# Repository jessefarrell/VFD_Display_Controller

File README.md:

<!-- PROJECT LOGO -->
<br />
<div align="center">

  <h1 align="center">VFD Module Controller - REV00</h1>

  <p align="center">
    The <a href="https://ckm-content.se.com/ckmContent/sfc/servlet.shepherd/document/download/0691H00000GYmavQAD">Power Measurement, ACM 3710</a> was a power meter released in 1989 which was discontinued in the "early 2000s".<br />
    These meters used an interesting, semi-custom, 20 character, 14 segment, Vacuum Fluorescent Display.
    <br />
    I have five of these VFD modules floating around my parts bin... so I made this controller board to interfce with them.
    <br />
    <br />
    <strong>STATUS - IN PROGRESS</strong>
    <br />
    <a href="https://youtube.com">View Demo</a> [PENDING]

  </p>
</div>

## Introduction
<!-- High level overview of what the project is and does -->
This VFD module controller was designed around a VFD module that was originally integrated into the <a href="https://ckm-content.se.com/ckmContent/sfc/servlet.shepherd/document/download/0691H00000GYmavQAD">ACM 3710</a>. Exact model numbers of the module seem to vary, but as far as I can tell they are all interchangeable. This module is the **ISE Electronics Corp, FU209SCPB-S4A** or **FU209SCPB-T60A**, and they seem to be a custom (undocumented) model that is similar to  **CU209SCPB-T20A**. The purpose of this project is to convert the VFD modules parallel bus interface into something configurable over USB, and to possible develop a few applications for the display.

## Motivation
<!-- Why I bothered making this -->
I'm a sucker for 7-segment displays and other interesting displays in general. So 14 segments on a VFD easily got my attention from the bin. A short dumpster dive later I found myself the proud owner of 5 VFD modules. All of the hard work of interfacing with the display is managed by the module, but I still need a way of controlling the 8bit data bus from the comfort of my desk. The fact that so much of the work has been offloaded onto the VFD module itself, makes this whole thing a good candidate for a "quick weekend project"...

## Features
- USB Serial Control
- Command Line Interface
- Write Character or String
- Shift Displayed String
- Delete Character
- Clear Screen

## How it Works
<!-- IMAGE: Block diagram -->
This project could, in theory, be as simple as a microcontroller driving the various I/O pins of the VFD module. The module itself consumes about 430-460mA during normal operation, from a single 5V power input (the module then converts that to a higher voltage for the VFD), leaving just enough headroom in the 500mA (5 unit load) USB spec to power the controller board I'm designing. Some flavour of AVR microcontroller would have been a good fit here, but my bin full of Pi Pico's is looking for a project, meaning I'll need some logic level translators. I also decided to include an optional barrel jack power input incase I want to stack multiple VFD modules together, or if the USB port isn't able to provide the 500mA.
<br />
<br />
Instead of providing a block diagram, this project is small enough to just review the schematic (shown below).

## Gallery

<!-- IMAGE: 2-3 supporting shots — schematic snippet, PCB layout, alternate angle render -->

## Status
I received PCBs 8/16/2026, and I recently ordered the connectors. This project will probably be closed later this month.

## License

---

Designed by Jesse Farrell — [info@shamrockcircuits.com](mailto:info@shamrockcircuits.com)

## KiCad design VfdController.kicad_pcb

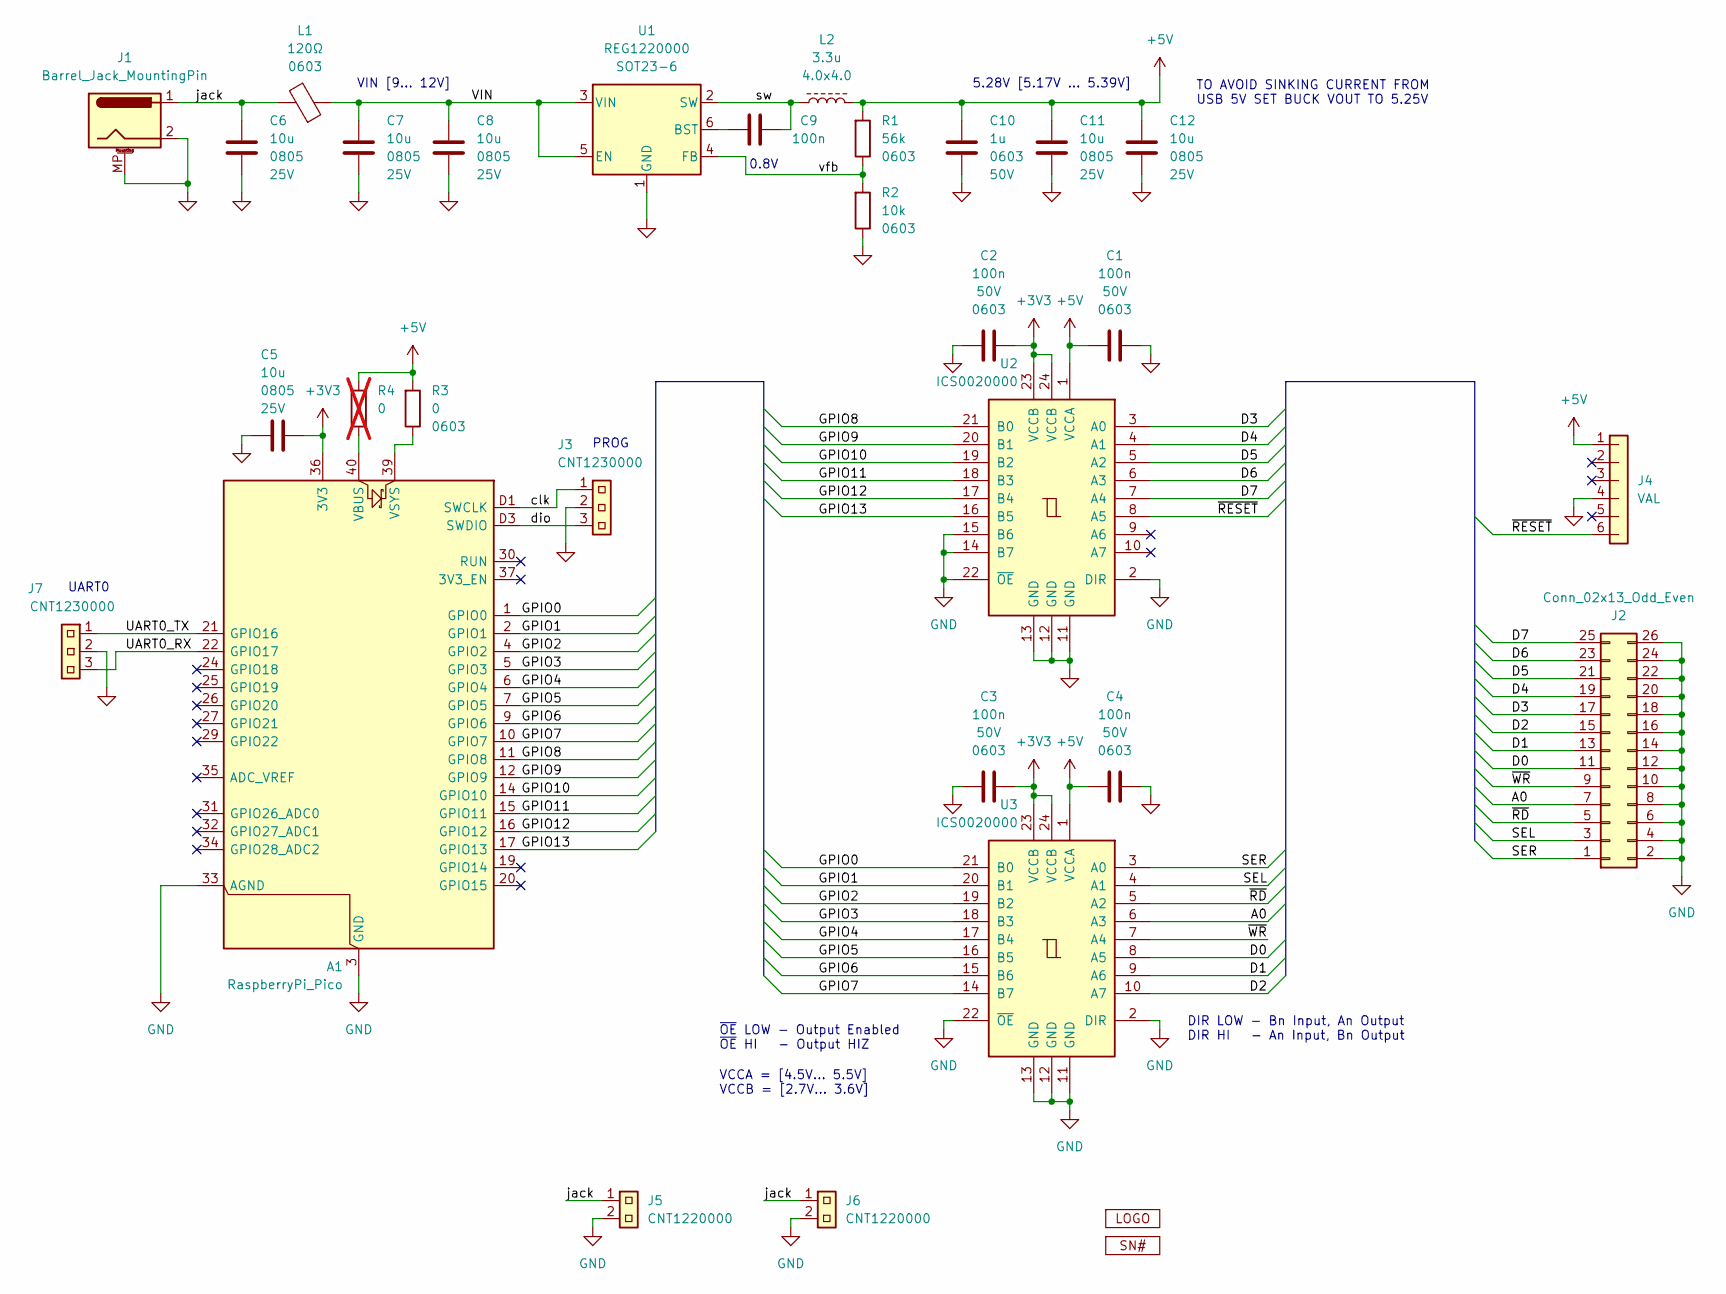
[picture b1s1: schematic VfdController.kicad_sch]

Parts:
A1: RaspberryPi_Pico; RaspberryPi_Pico_SMD_HandSolder
C1, C2, C3, C4: 100n; FTP-CAP-0001; Voltage Rating 50V; MPN_1 CC0603KRX7R9BB104; LCSC_1 C14663, BASIC
C5, C6, C7, C8, C11, C12: 10u; FTP-CAP-0002; Voltage Rating 25V; MPN_1 CL21A106KAYNNNE; LCSC_1 C15850
C9: 100n; FTP-CAP-0000; Voltage Rating 50V; MPN_1 CL05B104KB54PNC; LCSC_1 C307331
C10: 1u; FTP-CAP-0001; Voltage Rating 50V; MPN_1 CL10A105KB8NNNC; LCSC_1 C15849
G1: FTP-MRK-0002b
G2: FTP-MRK-0000
J1: Barrel_Jack_MountingPin; BarrelJack_GCT_DCJ200-10-A_Horizontal
J2: Conn_02x13_Odd_Even; IDC-Header_2x13_P2.54mm_Vertical
J3, J7: CNT1230000; FTP-CNT-0008; MPN_1 22284030; LCSC_1 C587036, EXT
J4: VAL; Molex_KK-396_A-41792-0006_1x06_P3.96mm_Horizontal
J5, J6: CNT1220000; FTP-CNT-0007; MPN_1 22284020; LCSC_1 C234182, EXT
L1: 120Ω; FTP-IND-0002; MPN_2 742792625; LCSC_1 C14709
L2: 3.3u; FTP-IND-0000; MPN_3 AWVF004040183R3M00; LCSC_3 C17220294
R1: 56k; FTP-RES-0001; MPN_1 RNCF0603BTE56K0; LCSC_1 C3958730
R2: 10k; FTP-RES-0001; MPN_1 RNCF0603BTE10K0; LCSC_1 C346560
R3: 0; FTP-RES-0001; MPN_1 0603WAF0000T5E; LCSC_1 C21189, BASIC
R4: 0; FTP-RES-0001; MPN_1 0603WAF0000T5E; LCSC_1 C21189, BASIC; not fitted
U1: REG1220000; Generic-SOT23-6; MPN_1 AP62150WU*; LCSC_1 C3194237
U2, U3: ICS0020000; Generic-TSSOP-24_4.4x7.8mm_P0.65mm; MPN_1 74LVC4245APW,118; LCSC_1 C6091, EXT

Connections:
+3V3: A1.36 (3V3), C2.2, C3.2, C5.1, U2.23 (VCCB), U2.24 (VCCB), U3.23 (VCCB), U3.24 (VCCB)
+5V: C1.1, C4.1, C10.1, C11.1, C12.1, J4.1, L2.2, R1.1, R3.1, R4.1, U2.1 (VCCA), U3.1 (VCCA)
/A0: J2.7, U3.6 (A3)
/D0: J2.11, U3.8 (A5)
/D1: J2.13, U3.9 (A6)
/D2: J2.15, U3.10 (A7)
/D3: J2.17, U2.3 (A0)
/D4: J2.19, U2.4 (A1)
/D5: J2.21, U2.5 (A2)
/D6: J2.23, U2.6 (A3)
/D7: J2.25, U2.7 (A4)
/GPIO0: A1.1 (GPIO0), U3.21 (B0)
/GPIO1: A1.2 (GPIO1), U3.20 (B1)
/GPIO2: A1.4 (GPIO2), U3.19 (B2)
/GPIO3: A1.5 (GPIO3), U3.18 (B3)
/GPIO4: A1.6 (GPIO4), U3.17 (B4)
/GPIO5: A1.7 (GPIO5), U3.16 (B5)
/GPIO6: A1.9 (GPIO6), U3.15 (B6)
/GPIO7: A1.10 (GPIO7), U3.14 (B7)
/GPIO8: A1.11 (GPIO8), U2.21 (B0)
/GPIO9: A1.12 (GPIO9), U2.20 (B1)
/GPIO10: A1.14 (GPIO10), U2.19 (B2)
/GPIO11: A1.15 (GPIO11), U2.18 (B3)
/GPIO12: A1.16 (GPIO12), U2.17 (B4)
/GPIO13: A1.17 (GPIO13), U2.16 (B5)
/SEL: J2.3, U3.4 (A1)
/SER: J2.1, U3.3 (A0)
/UART0_RX: A1.22 (GPIO17), J7.3
/UART0_TX: A1.21 (GPIO16), J7.1
/VIN: C7.1, C8.1, L1.1, U1.3 (VIN), U1.5 (EN)
/clk: A1.D1 (SWCLK), J3.1
/dio: A1.D3 (SWDIO), J3.3
/jack: C6.1, J1.1, J5.1, J6.1, L1.2
/sw: C9.1, L2.1, U1.2 (SW)
/vfb: R1.2, R2.1, U1.4 (FB)
/~RD: J2.5, U3.5 (A2)
/~RESET: J4.6, U2.8 (A5)
/~WR: J2.9, U3.7 (A4)
GND: A1.3 (GND), A1.8 (GND), A1.13 (GND), A1.18 (GND), A1.23 (GND), A1.28 (GND), A1.33 (AGND), A1.38 (GND), A1.D2 (GND), C1.2, C2.1, C3.1, C4.2, C5.2, C6.2, C7.2, C8.2, C10.2, C11.2, C12.2, J1.2, J1.MP (MountPin_MP), J2.2, J2.4, J2.6, J2.8, J2.10, J2.12, J2.14, J2.16, J2.18, J2.20, J2.22, J2.24, J2.26, J3.2, J4.4, J5.2, J6.2, J7.2, R2.2, U1.1 (GND), U2.2 (DIR), U2.11 (GND), U2.12 (GND), U2.13 (GND), U2.14 (B7), U2.15 (B6), U2.22 (~OE), U3.2 (DIR), U3.11 (GND), U3.12 (GND), U3.13 (GND), U3.22 (~OE)
unnamed: A1.40 (VBUS), R4.2
unnamed: A1.39 (VSYS), R3.2
unnamed: C9.2, U1.6 (BST)

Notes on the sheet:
DIR LOW - Bn Input, An Output DIR HI - An Input, Bn Output
VCCA = [4.5V... 5.5V] VCCB = [2.7V... 3.6V]
5.28V [5.17V ... 5.39V]
PROG
0.8V
~{OE} LOW - Output Enabled ~{OE} HI - Output HIZ
UART0
TO AVOID SINKING CURRENT FROM USB 5V SET BUCK VOUT TO 5.25V
VIN [9... 12V]

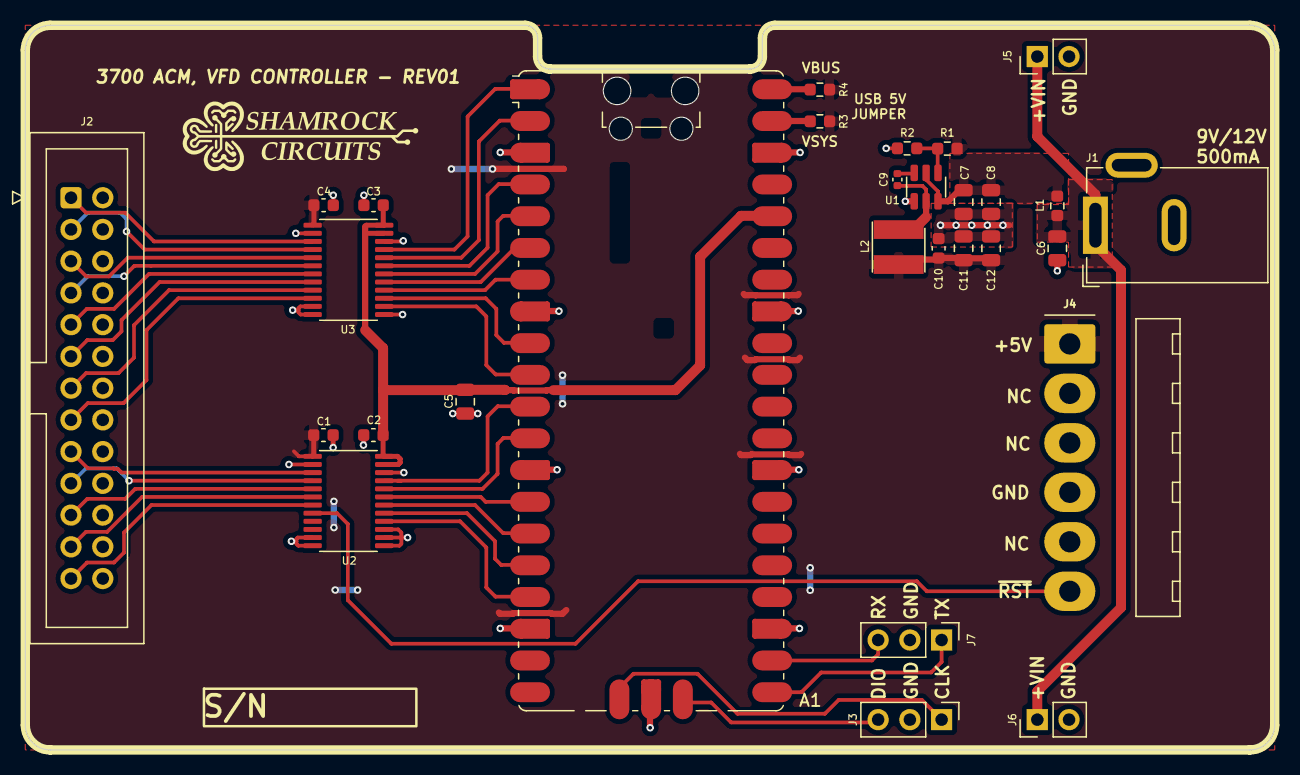
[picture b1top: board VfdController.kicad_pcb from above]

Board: 2 copper layers, 100.0 x 58.0 mm, 31 parts (0 on the bottom side), 42 nets.

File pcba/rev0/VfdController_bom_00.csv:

IPN,Reference,Qty,Value,Exclude from BOM,Footprint,Package,MFN_1,MPN_1,LCSC_1
N/A,A1,1,RaspberryPi_Pico,,Module:RaspberryPi_Pico_SMD_HandSolder,,,,
CAP-000-1042,"C1,C2,C3,C4",4,100n,,0-CAP:FTP-CAP-0001,603,Samsung,CC0603KRX7R9BB104,"C14663, BASIC"
CAP-007-1061,"C5,C6,C7,C8,C11,C12",6,10u,,0-CAP:FTP-CAP-0002,805,Samsung,CL21A106KAYNNNE,C15850
CAP-001-1042,C9,1,100n,,0-CAP:FTP-CAP-0000,402,Samsung,CL05B104KB54PNC,C307331
CAP-003-1051,C10,1,1u,,0-CAP:FTP-CAP-0001,603,Samsung,CL10A105KB8NNNC,C15849
N/A,J1,1,Barrel_Jack_MountingPin,,Connector_BarrelJack:BarrelJack_GCT_DCJ200-10-A_Horizontal,,,,
N/A,J2,1,Conn_02x13_Odd_Even,,Connector_IDC:IDC-Header_2x13_P2.54mm_Vertical,,,,
CNT-123-0000,J3,1,CNT1230000,,0-CNT:FTP-CNT-0008,,Molex,22284030,"C587036, EXT"
N/A,J4,1,VAL,,Connector_Molex:Molex_KK-396_A-41792-0006_1x06_P3.96mm_Horizontal,,,,
CNT-122-0000,"J5,J6",2,CNT1220000,,0-CNT:FTP-CNT-0007,,Molex,22284020,"C234182, EXT"
IND-203-1202,L1,1,120Ω,,0-IND:FTP-IND-0002,603,Murata,BLM18PG121SN1D,C14709
IND-002-3304,L2,1,3.3u,,0-IND:FTP-IND-0000,4.0x4.0,Vishay,VLS4020CX-3R3M-H,C6745793
RES-006-5604,R1,1,56k,,0-RES:FTP-RES-0001,603,Stackpole Electronics,RNCF0603BTE56K0,C3958730
RES-006-1004,R2,1,10k,,0-RES:FTP-RES-0001,603,Stackpole Electronics,RNCF0603BTE10K0,C346560
RES-000-0000,R3,1,0,,0-RES:FTP-RES-0001,603,UNI-ROYAL,0603WAF0000T5E,"C21189, BASIC"
REG-122-0000,U1,1,REG1220000,,1-PACKAGES:Generic-SOT23-6,SOT23-6,Diodes Inc.,AP62150WU*,C3194237
ICS-002-0000,"U2,U3",2,ICS0020000,,1-PACKAGES:Generic-TSSOP-24_4.4x7.8mm_P0.65mm,TSSOP-24 (4.40mm),Nexperia,"74LVC4245APW,118","C6091, EXT"

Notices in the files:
README.md:
[License: CERN-OHL-P](LICENSE)
